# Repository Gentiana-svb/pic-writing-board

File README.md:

# pic-writing-board

PIC writing board for DIP package with auto guess pin count.

## Core Components

|            |                   |
| ---------- | ----------------- |
| Analog MUX | TMUX1309BQBR      |
| MCU        | PIC18F27Q10T-I/ML |
| Comparator | LM2901Q4T         |
| SSR        | TLP172AM          |
| LDO        | NJM2845           |
| Power SW   | TCP8407           |

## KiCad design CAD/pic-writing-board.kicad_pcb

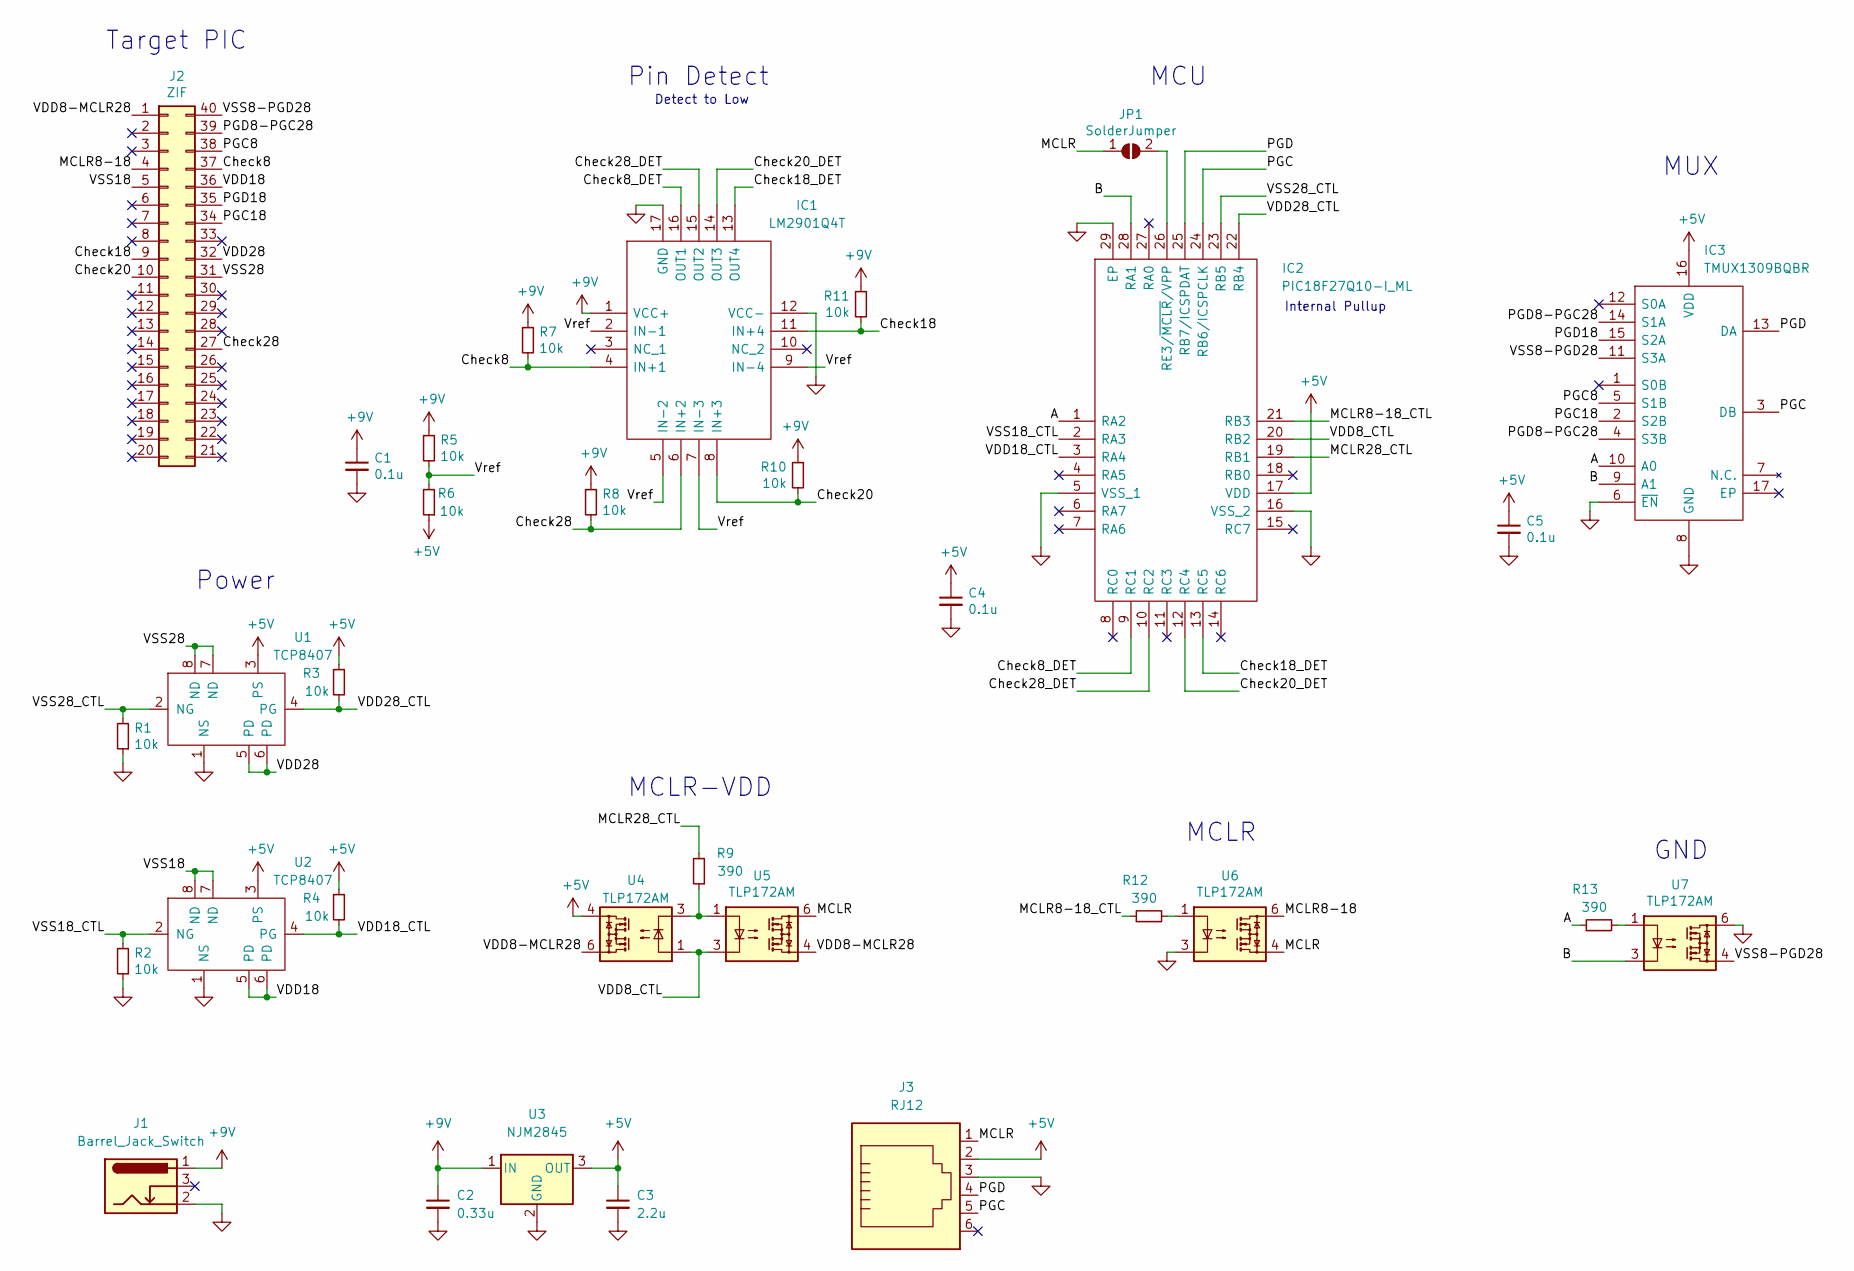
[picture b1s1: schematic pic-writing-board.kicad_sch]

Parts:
C1, C4, C5: 0.1u; C_0603_1608Metric
C2: 0.33u; C_0603_1608Metric
C3: 2.2u; C_0603_1608Metric
IC1: LM2901Q4T; QFN50P300X300X100-17N; Mouser Part Number 511-LM2901Q4T
IC2: PIC18F27Q10-I_ML; QFN65P600X600X100-29N-D; Mouser Part Number 579-PIC18F27Q10-I/ML
IC3: TMUX1309BQBR; Mouser Part Number 595-TMUX1309BQBR
J1: Barrel_Jack_Switch; BarrelJack_Wuerth_6941xx301002
J2: ZIF
J3: RJ12; 6P6C
JP1: SolderJumper; SolderJumper-2_P1.3mm_Open_RoundedPad1.0x1.5mm
R1, R2, R3, R4, R5, R6, R7, R8, R10, R11: 10k; R_0603_1608Metric
R9, R12, R13: 390; R_0603_1608Metric
U1, U2: TCP8407; SOP-8_3.9x4.9mm_P1.27mm
U3: NJM2845; TO-252-2
U4, U5, U6, U7: TLP172AM; SOIC-4_4.55x3.7mm_P2.54mm

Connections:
+5V: C3.1, C4.1, C5.1, IC2.17 (VDD), IC3.16 (VDD), J3.2, R3.1, R4.1, R6.1, U1.3 (PS), U2.3 (PS), U3.3 (OUT), U4.4
+9V: C1.1, C2.1, IC1.1 (VCC+), J1.1, R5.1, R7.1, R8.1, R10.1, R11.1, U3.1 (IN)
/A: IC2.1 (RA2), IC3.10 (A0), R13.1
/B: IC2.28 (RA1), IC3.9 (A1), U7.3
/Check8: IC1.4 (IN+1), J2.37, R7.2
/Check8_DET: IC1.16 (OUT1), IC2.9 (RC1)
/Check18: IC1.11 (IN+4), J2.9, R11.2
/Check18_DET: IC1.13 (OUT4), IC2.13 (RC5)
/Check20: IC1.8 (IN+3), J2.10, R10.2
/Check20_DET: IC1.14 (OUT3), IC2.12 (RC4)
/Check28: IC1.6 (IN+2), J2.27, R8.2
/Check28_DET: IC1.15 (OUT2), IC2.10 (RC2)
/MCLR: J3.1, JP1.1 (A), U5.6, U6.4
/MCLR8-18: J2.4, U6.6
/MCLR8-18_CTL: IC2.21 (RB3), R12.1
/MCLR28_CTL: IC2.19 (RB1), R9.2
/PGC: IC2.24 (RB6/ICSPCLK), IC3.3 (DB), J3.5
/PGC8: IC3.5 (S1B), J2.38
/PGC18: IC3.2 (S2B), J2.34
/PGD: IC2.25 (RB7/ICSPDAT), IC3.13 (DA), J3.4
/PGD8-PGC28: IC3.4 (S3B), IC3.14 (S1A), J2.39
/PGD18: IC3.15 (S2A), J2.35
/VDD8-MCLR28: J2.1, U4.6, U5.4
/VDD8_CTL: IC2.20 (RB2), U4.1, U5.3
/VDD18: J2.36, U2.5 (PD), U2.6 (PD)
/VDD18_CTL: IC2.3 (RA4), R4.2, U2.4 (PG)
/VDD28: J2.32, U1.5 (PD), U1.6 (PD)
/VDD28_CTL: IC2.22 (RB4), R3.2, U1.4 (PG)
/VSS8-PGD28: IC3.11 (S3A), J2.40, U7.4
/VSS18: J2.5, U2.7 (ND), U2.8 (ND)
/VSS18_CTL: IC2.2 (RA3), R2.2, U2.2 (NG)
/VSS28: J2.31, U1.7 (ND), U1.8 (ND)
/VSS28_CTL: IC2.23 (RB5), R1.2, U1.2 (NG)
/Vref: IC1.2 (IN-1), IC1.5 (IN-2), IC1.7 (IN-3), IC1.9 (IN-4), R5.2, R6.2
GND: C1.2, C2.2, C3.2, C4.2, C5.2, IC1.12 (VCC-), IC1.17 (GND), IC2.5 (VSS_1), IC2.16 (VSS_2), IC2.29 (EP), IC3.6 (~EN), IC3.8 (GND), J1.2, J3.3, R1.1, R2.1, U1.1 (NS), U2.1 (NS), U3.2 (GND), U6.3, U7.6
unnamed: IC2.26 (RE3/~MCLR/VPP), JP1.2 (B)
unnamed: R9.1, U4.3, U5.1
unnamed: R12.2, U6.1
unnamed: R13.2, U7.1

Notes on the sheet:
MCU
MCLR
Internal Pullup
GND
Target PIC
MCLR-VDD
Pin Detect
Power
Detect to Low
MUX

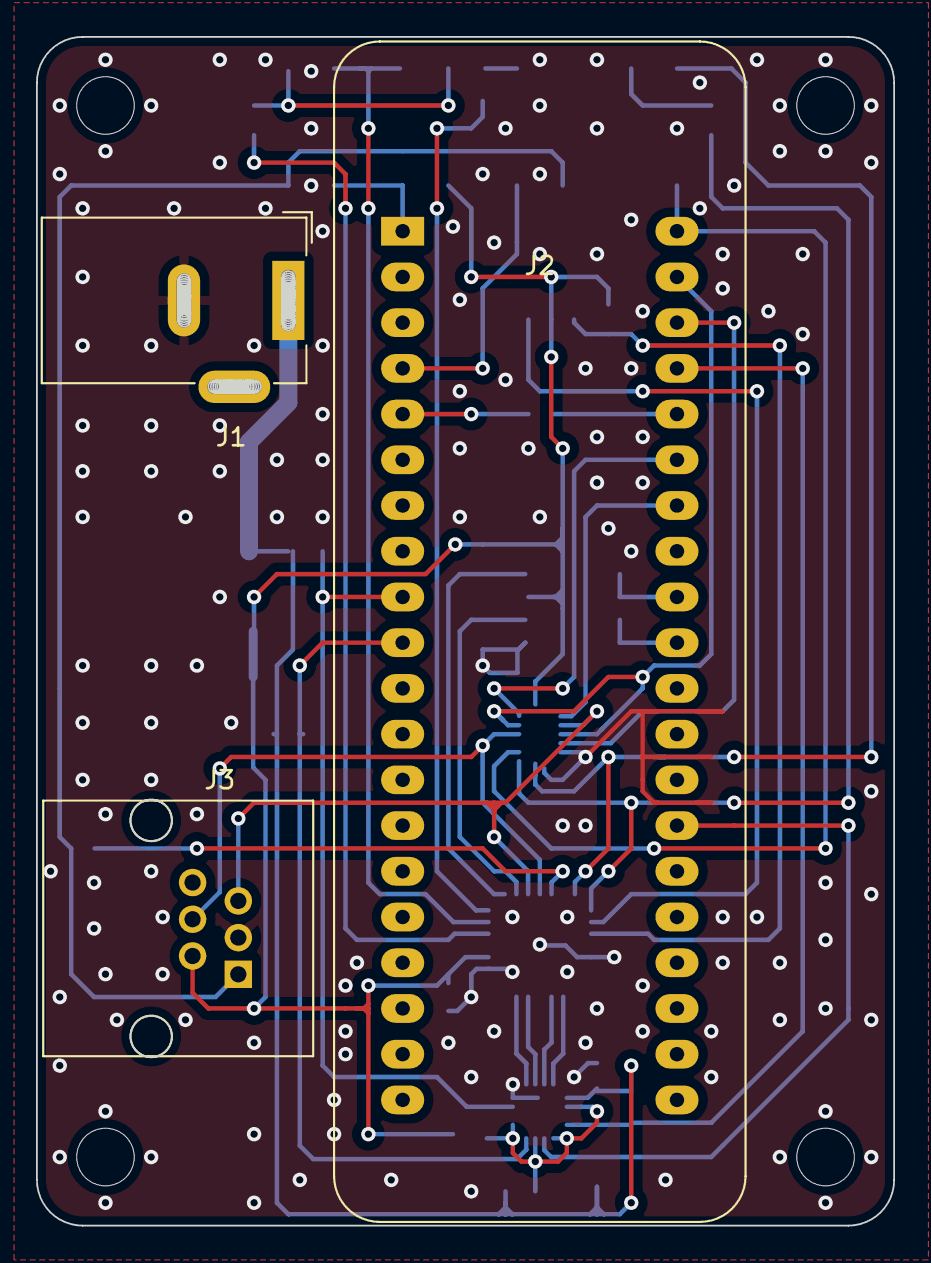
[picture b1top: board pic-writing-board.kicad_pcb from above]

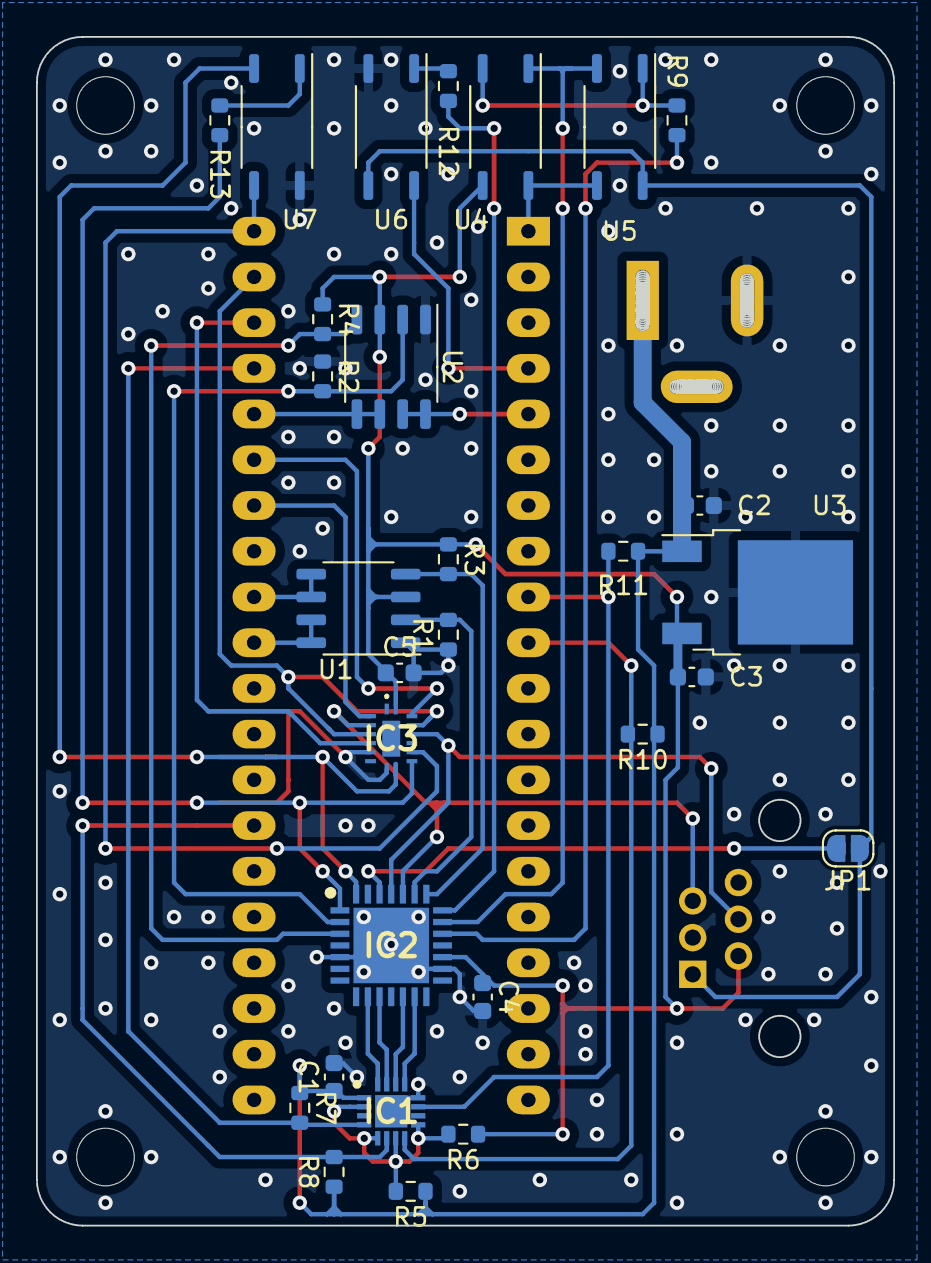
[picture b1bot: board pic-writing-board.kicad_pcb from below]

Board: 2 copper layers, 47.6 x 66.0 mm, 32 parts (29 on the bottom side), 39 nets.

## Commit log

2022-11-13 update ignore setting
2022-11-13 add base files
2022-11-13 add lib
2022-11-13 add parts
2022-11-14 migrate lib
2022-11-14 make sch
2022-11-14 add pcb lib
2022-11-14 import parts
2022-11-14 adjust port assign
2022-11-14 make pcb
2022-11-14 adjust sch
2022-11-15 fill pcb
2022-11-15 add gerber
